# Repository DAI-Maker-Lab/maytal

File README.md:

<<<<<<< HEAD
# Maytal
Maytal is the temporary name for an open source hardware project that aims to empower local Indonesian water utilities (PDAMs) to track pressure throughout their distribution systems, enabling them to operate more efficiently. The current design is a proof-of-concept prototype to test initial parameters and constraints. The bill of materials cost is about $180 and most parts are available locally in Indonesia.
=======
#Maytal

Maytal is the temporary name for an open source hardware project that aims to empower local Indonesian water utilities (PDAMs) to track pressure throughout their distribution systems, enabling them to operate more efficiently. The current design is a proof-of-concept prototype to test initial parameters and constraints. The bill of materials cost is about $180 and most parts are available locally in Indonesia.
>>>>>>> origin/master

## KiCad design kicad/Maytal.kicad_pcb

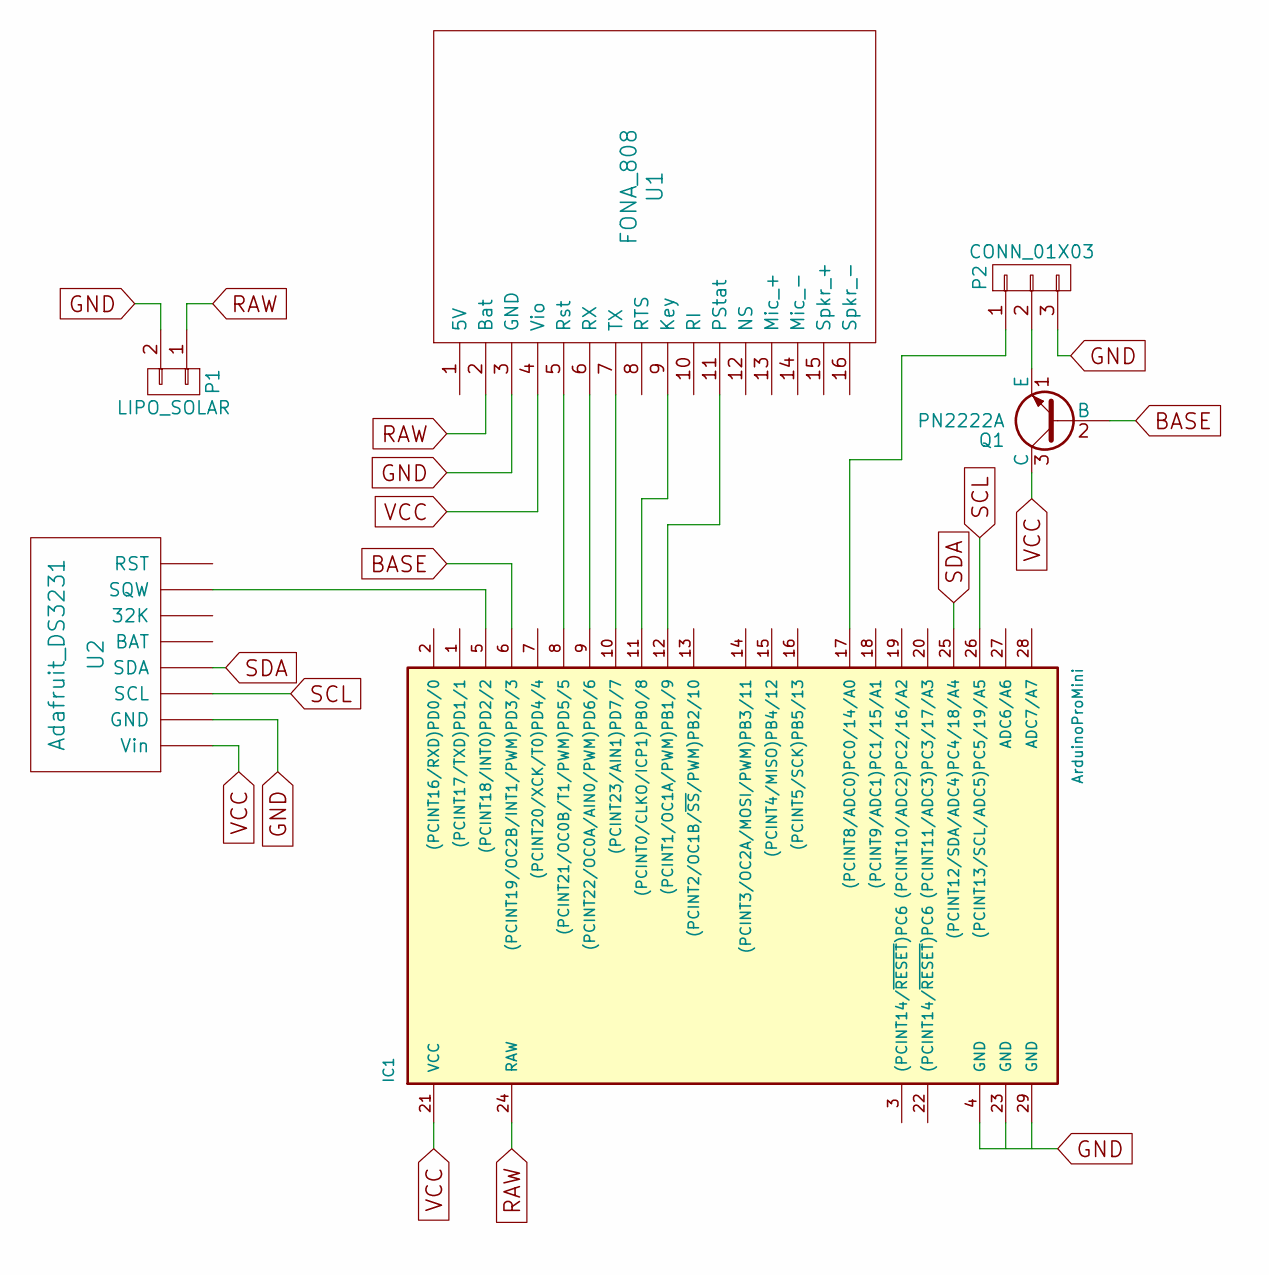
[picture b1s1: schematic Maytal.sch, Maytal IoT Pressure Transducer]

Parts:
IC1: ArduinoProMini; Arduino_Pro_Mini
P1: LIPO_SOLAR; Adafruit_LiPo_Solar
P2: CONN_01X03; TerminalBlock_Pheonix_PT-3.5mm_3pol
Q1: PN2222A; TO-92_Inline_Narrow_Oval
U1: FONA_808
U2: Adafruit_DS3231

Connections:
BASE: IC1.6 ((PCINT19/OC2B/INT1/PWM)PD3/3), Q1.2 (B)
GND: IC1.4 (GND), P1.2, P2.3, U1.3 (GND), U2.2 (GND)
unnamed: IC1.5 ((PCINT18/INT0)PD2/2), U2.7 (SQW)
unnamed: IC1.8 ((PCINT21/OC0B/T1/PWM)PD5/5), U1.5 (Rst)
unnamed: IC1.9 ((PCINT22/OC0A/AIN0/PWM)PD6/6), U1.6 (RX)
unnamed: IC1.10 ((PCINT23/AIN1)PD7/7), U1.7 (TX)
unnamed: IC1.11 ((PCINT0/CLKO/ICP1)PB0/8), U1.9 (Key)
unnamed: IC1.12 ((PCINT1/OC1A/PWM)PB1/9), U1.11 (PStat)
unnamed: IC1.17 ((PCINT8/ADC0)PC0/14/A0), P2.1
unnamed: P2.2, Q1.1 (E)
RAW: IC1.24 (RAW), P1.1, U1.2 (Bat)
SCL: IC1.26 ((PCINT13/SCL/ADC5)PC5/19/A5), U2.3 (SCL)
SDA: IC1.25 ((PCINT12/SDA/ADC4)PC4/18/A4), U2.4 (SDA)
VCC: IC1.21 (VCC), Q1.3 (C), U1.4 (Vio), U2.1 (Vin)

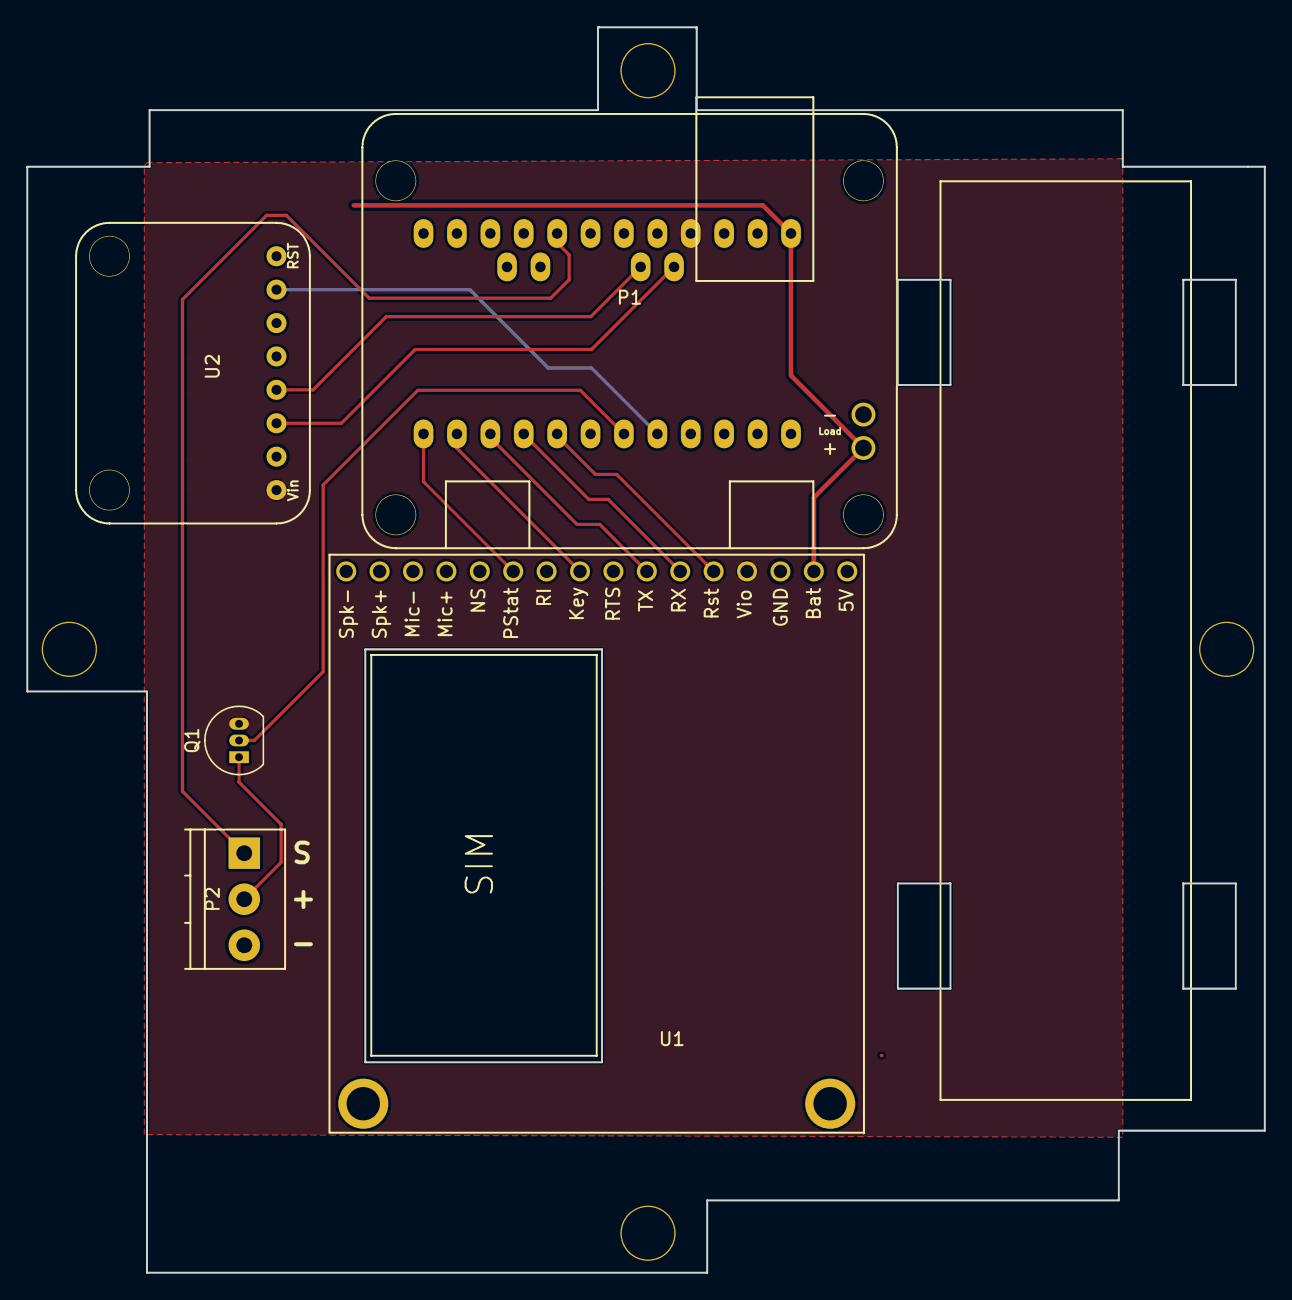
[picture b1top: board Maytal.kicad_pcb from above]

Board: 2 copper layers, 94.1 x 94.7 mm, 6 parts (1 on the bottom side), 14 nets.

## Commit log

2017-04-21 Fixed typo in README.md
2017-04-21 Merge remote-tracking branch 'origin/master'
    # Conflicts:
    # README.md
2017-08-01 Rerouted power bus
